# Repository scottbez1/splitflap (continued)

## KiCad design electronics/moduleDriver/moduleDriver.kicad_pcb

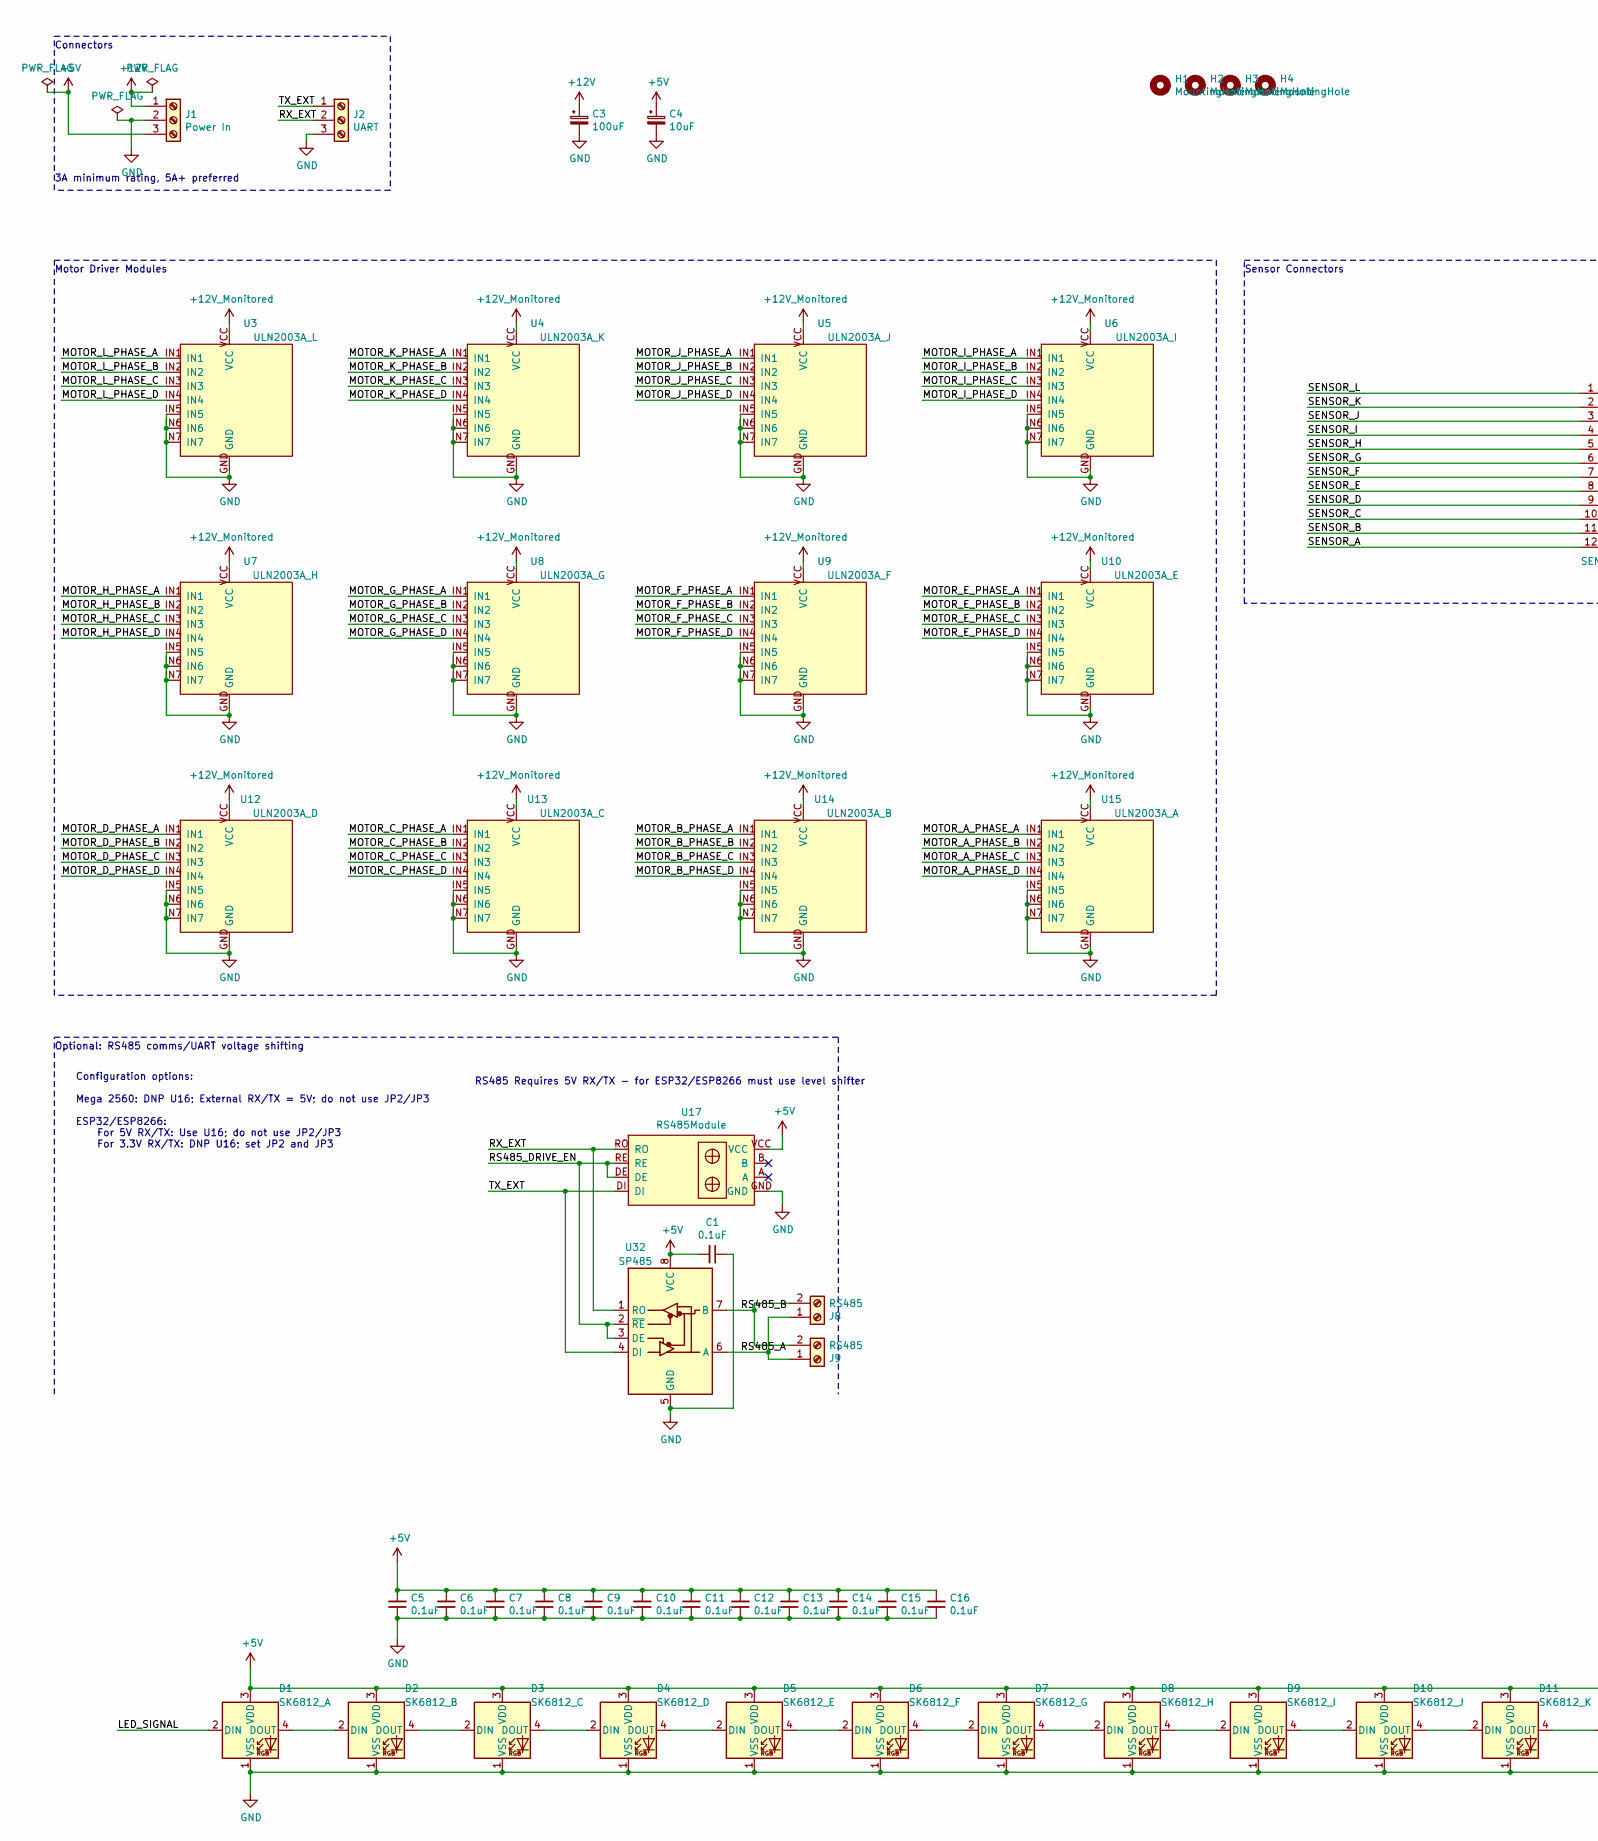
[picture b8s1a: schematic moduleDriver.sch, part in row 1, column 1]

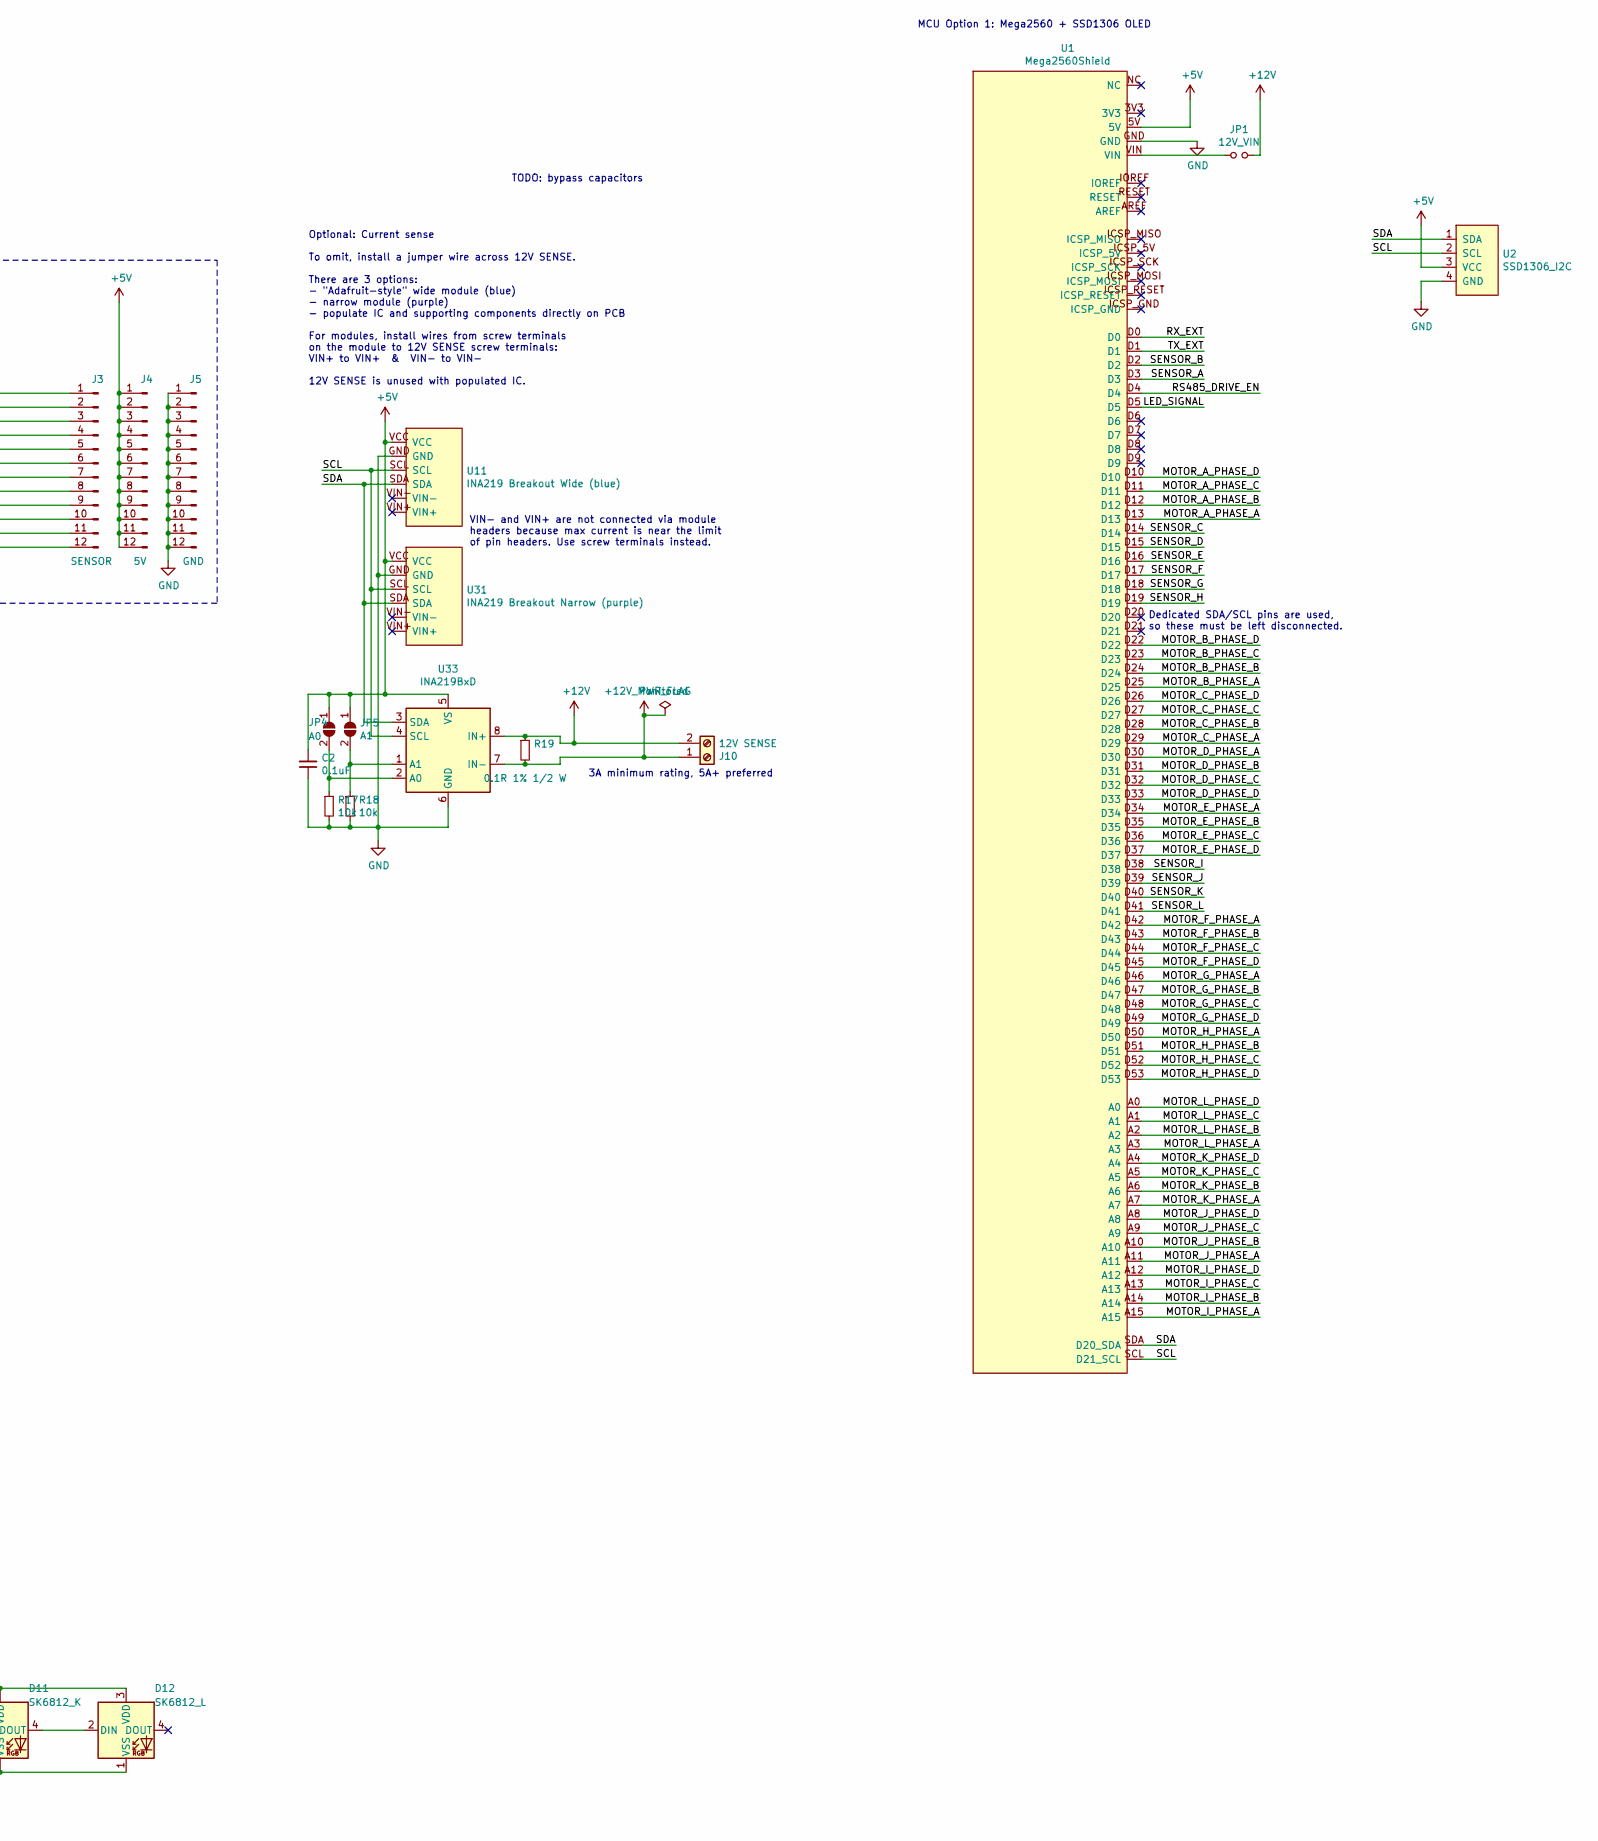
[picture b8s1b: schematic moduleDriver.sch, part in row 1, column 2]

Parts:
C1, C2, C5, C6, C7, C8, C9, C10, C11, C12, C13, C14, C15, C16: 0.1uF; C_0805_2012Metric_Pad1.15x1.40mm_HandSolder
C3: 100uF; CP_Radial_D10.0mm_P3.50mm
C4: 10uF; CP_Radial_D6.3mm_P2.50mm
D1: SK6812_A; LED_SK6812_PLCC4_5.0x5.0mm_P3.2mm
D2: SK6812_B; LED_SK6812_PLCC4_5.0x5.0mm_P3.2mm
D3: SK6812_C; LED_SK6812_PLCC4_5.0x5.0mm_P3.2mm
D4: SK6812_D; LED_SK6812_PLCC4_5.0x5.0mm_P3.2mm
D5: SK6812_E; LED_SK6812_PLCC4_5.0x5.0mm_P3.2mm
D6: SK6812_F; LED_SK6812_PLCC4_5.0x5.0mm_P3.2mm
D7: SK6812_G; LED_SK6812_PLCC4_5.0x5.0mm_P3.2mm
D8: SK6812_H; LED_SK6812_PLCC4_5.0x5.0mm_P3.2mm
D9: SK6812_I; LED_SK6812_PLCC4_5.0x5.0mm_P3.2mm
D10: SK6812_J; LED_SK6812_PLCC4_5.0x5.0mm_P3.2mm
D11: SK6812_K; LED_SK6812_PLCC4_5.0x5.0mm_P3.2mm
D12: SK6812_L; LED_SK6812_PLCC4_5.0x5.0mm_P3.2mm
H1, H2, H3, H4: MountingHole; MountingHole_4.3mm_M4_ISO7380_Pad
J1: Power In; TerminalBlock_bornier-3_P5.08mm
J2: UART; TerminalBlock_bornier-3_P5.08mm
J3: SENSOR; PinHeader_1x12_P2.54mm_Vertical
J4: 5V; PinHeader_1x12_P2.54mm_Vertical
J5: GND; PinHeader_1x12_P2.54mm_Vertical
J8, J9: RS485; TerminalBlock_bornier-2_P5.08mm
J10: 12V SENSE; TerminalBlock_bornier-2_P5.08mm
JP1: 12V_VIN; PinHeader_1x02_P2.54mm_Vertical
JP4: A0; SolderJumper-2_P1.3mm_Open_TrianglePad1.0x1.5mm
JP5: A1; SolderJumper-2_P1.3mm_Open_TrianglePad1.0x1.5mm
R17, R18: 10k; R_0805_2012Metric_Pad1.15x1.40mm_HandSolder
R19: 0.1R 1% 1/2 W; R_2512_6332Metric_Pad1.52x3.35mm_HandSolder
U1: Mega2560Shield; Mega2560Shield_Modified
U2: SSD1306_I2C; SSD1306_128x32
U3: ULN2003A_L; ULN2003AModule_No_EN_No_FSilk
U4: ULN2003A_K; ULN2003AModule_No_EN_No_FSilk
U5: ULN2003A_J; ULN2003AModule_No_EN_No_FSilk
U6: ULN2003A_I; ULN2003AModule_No_EN_No_FSilk
U7: ULN2003A_H; ULN2003AModule_No_EN_No_FSilk
U8: ULN2003A_G; ULN2003AModule_No_EN_No_FSilk
U9: ULN2003A_F; ULN2003AModule_No_EN_No_FSilk
U10: ULN2003A_E; ULN2003AModule_No_EN_No_FSilk
U11: INA219 Breakout Wide (blue); INA219_LARGE
U12: ULN2003A_D; ULN2003AModule_No_EN_No_FSilk
U13: ULN2003A_C; ULN2003AModule_No_EN_No_FSilk
U14: ULN2003A_B; ULN2003AModule_No_EN_No_FSilk
U15: ULN2003A_A; ULN2003AModule_No_EN_No_FSilk
U17: RS485Module
U31: INA219 Breakout Narrow (purple); INA219_SMALL
U32: SP485; SOIC-8_3.9x4.9mm_P1.27mm
U33: INA219BxD; SOIC-8_3.9x4.9mm_P1.27mm

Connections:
+5V: C1.2, C2.2, C4.1, C5.2, C6.2, C7.2, C8.2, C9.2, C10.2, C11.2, C12.2, C13.2, C14.2, C15.2, C16.2, D1.3 (VDD), D2.3 (VDD), D3.3 (VDD), D4.3 (VDD), D5.3 (VDD), D6.3 (VDD), D7.3 (VDD), D8.3 (VDD), D9.3 (VDD), D10.3 (VDD), D11.3 (VDD), D12.3 (VDD), J1.3, J4.1, J4.2, J4.3, J4.4, J4.5, J4.6, J4.7, J4.8, J4.9, J4.10, J4.11, J4.12, JP4.1 (A), JP5.1 (A), U1.5V, U2.3 (VCC), U11.VCC, U17.VCC, U31.VCC, U32.8 (VCC), U33.5 (VS)
+12V: C3.1, J1.1, J10.2, JP1.2, R19.1, U33.8 (IN+)
+12V_Monitored: J10.1, R19.2, U3.VCC, U4.VCC, U5.VCC, U6.VCC, U7.VCC, U8.VCC, U9.VCC, U10.VCC, U12.VCC, U13.VCC, U14.VCC, U15.VCC, U33.7 (IN-)
/LED_SIGNAL: D1.2 (DIN), U1.D5
/MOTOR_A_PHASE_A: U1.D13, U15.IN1
/MOTOR_A_PHASE_B: U1.D12, U15.IN2
/MOTOR_A_PHASE_C: U1.D11, U15.IN3
/MOTOR_A_PHASE_D: U1.D10, U15.IN4
/MOTOR_B_PHASE_A: U1.D25, U14.IN1
/MOTOR_B_PHASE_B: U1.D24, U14.IN2
/MOTOR_B_PHASE_C: U1.D23, U14.IN3
/MOTOR_B_PHASE_D: U1.D22, U14.IN4
/MOTOR_C_PHASE_A: U1.D29, U13.IN1
/MOTOR_C_PHASE_B: U1.D28, U13.IN2
/MOTOR_C_PHASE_C: U1.D27, U13.IN3
/MOTOR_C_PHASE_D: U1.D26, U13.IN4
/MOTOR_D_PHASE_A: U1.D30, U12.IN1
/MOTOR_D_PHASE_B: U1.D31, U12.IN2
/MOTOR_D_PHASE_C: U1.D32, U12.IN3
/MOTOR_D_PHASE_D: U1.D33, U12.IN4
/MOTOR_E_PHASE_A: U1.D34, U10.IN1
/MOTOR_E_PHASE_B: U1.D35, U10.IN2
/MOTOR_E_PHASE_C: U1.D36, U10.IN3
/MOTOR_E_PHASE_D: U1.D37, U10.IN4
/MOTOR_F_PHASE_A: U1.D42, U9.IN1
/MOTOR_F_PHASE_B: U1.D43, U9.IN2
/MOTOR_F_PHASE_C: U1.D44, U9.IN3
/MOTOR_F_PHASE_D: U1.D45, U9.IN4
/MOTOR_G_PHASE_A: U1.D46, U8.IN1
/MOTOR_G_PHASE_B: U1.D47, U8.IN2
/MOTOR_G_PHASE_C: U1.D48, U8.IN3
/MOTOR_G_PHASE_D: U1.D49, U8.IN4
/MOTOR_H_PHASE_A: U1.D50, U7.IN1
/MOTOR_H_PHASE_B: U1.D51, U7.IN2
/MOTOR_H_PHASE_C: U1.D52, U7.IN3
/MOTOR_H_PHASE_D: U1.D53, U7.IN4
/MOTOR_I_PHASE_A: U1.A15, U6.IN1
/MOTOR_I_PHASE_B: U1.A14, U6.IN2
/MOTOR_I_PHASE_C: U1.A13, U6.IN3
/MOTOR_I_PHASE_D: U1.A12, U6.IN4
/MOTOR_J_PHASE_A: U1.A11, U5.IN1
/MOTOR_J_PHASE_B: U1.A10, U5.IN2
/MOTOR_J_PHASE_C: U1.A9, U5.IN3
/MOTOR_J_PHASE_D: U1.A8, U5.IN4
/MOTOR_K_PHASE_A: U1.A7, U4.IN1
/MOTOR_K_PHASE_B: U1.A6, U4.IN2
/MOTOR_K_PHASE_C: U1.A5, U4.IN3
/MOTOR_K_PHASE_D: U1.A4, U4.IN4
/MOTOR_L_PHASE_A: U1.A3, U3.IN1
/MOTOR_L_PHASE_B: U1.A2, U3.IN2
/MOTOR_L_PHASE_C: U1.A1, U3.IN3
/MOTOR_L_PHASE_D: U1.A0, U3.IN4
/RS485_A: J8.1, J9.1, U32.6 (A)
/RS485_B: J8.2, J9.2, U32.7 (B)
/RS485_DRIVE_EN: U1.D4, U17.DE, U17.RE, U32.2 (~RE), U32.3 (DE)
/RX_EXT: J2.2, U1.D0, U17.RO, U32.1 (RO)
/SCL: U1.SCL (D21_SCL), U2.2 (SCL), U11.SCL, U31.SCL, U33.4 (SCL)
/SDA: U1.SDA (D20_SDA), U2.1 (SDA), U11.SDA, U31.SDA, U33.3 (SDA)
/SENSOR_A: J3.12, U1.D3
/SENSOR_B: J3.11, U1.D2
/SENSOR_C: J3.10, U1.D14
/SENSOR_D: J3.9, U1.D15
/SENSOR_E: J3.8, U1.D16
/SENSOR_F: J3.7, U1.D17
/SENSOR_G: J3.6, U1.D18
/SENSOR_H: J3.5, U1.D19
/SENSOR_I: J3.4, U1.D38
/SENSOR_J: J3.3, U1.D39
/SENSOR_K: J3.2, U1.D40
/SENSOR_L: J3.1, U1.D41
/TX_EXT: J2.1, U1.D1, U17.DI, U32.4 (DI)
GND: C1.1, C2.1, C3.2, C4.2, C5.1, C6.1, C7.1, C8.1, C9.1, C10.1, C11.1, C12.1, C13.1, C14.1, C15.1, C16.1, D1.1 (VSS), D2.1 (VSS), D3.1 (VSS), D4.1 (VSS), D5.1 (VSS), D6.1 (VSS), D7.1 (VSS), D8.1 (VSS), D9.1 (VSS), D10.1 (VSS), D11.1 (VSS), D12.1 (VSS), J1.2, J2.3, J5.1, J5.2, J5.3, J5.4, J5.5, J5.6, J5.7, J5.8, J5.9, J5.10, J5.11, J5.12, R17.2, R18.2, U1.GND, U2.4 (GND), U3.GND, U3.IN5, U3.IN6, U3.IN7, U4.GND, U4.IN5, U4.IN6, U4.IN7, U5.GND, U5.IN5, U5.IN6, U5.IN7, U6.GND, U6.IN5, U6.IN6, U6.IN7, U7.GND, U7.IN5, U7.IN6, U7.IN7, U8.GND, U8.IN5, U8.IN6, U8.IN7, U9.GND, U9.IN5, U9.IN6, U9.IN7, U10.GND, U10.IN5, U10.IN6, U10.IN7, U11.GND, U12.GND, U12.IN5, U12.IN6, U12.IN7, U13.GND, U13.IN5, U13.IN6, U13.IN7, U14.GND, U14.IN5, U14.IN6, U14.IN7, U15.GND, U15.IN5, U15.IN6, U15.IN7, U17.GND, U31.GND, U32.5 (GND), U33.6 (GND)
unnamed: D1.4 (DOUT), D2.2 (DIN)
unnamed: D2.4 (DOUT), D3.2 (DIN)
unnamed: D3.4 (DOUT), D4.2 (DIN)
unnamed: D4.4 (DOUT), D5.2 (DIN)
unnamed: D5.4 (DOUT), D6.2 (DIN)
unnamed: D6.4 (DOUT), D7.2 (DIN)
unnamed: D7.4 (DOUT), D8.2 (DIN)
unnamed: D8.4 (DOUT), D9.2 (DIN)
unnamed: D9.4 (DOUT), D10.2 (DIN)
unnamed: D10.4 (DOUT), D11.2 (DIN)
unnamed: D11.4 (DOUT), D12.2 (DIN)
unnamed: JP1.1, U1.VIN
unnamed: JP4.2 (B), R17.1, U33.2 (A0)
unnamed: JP5.2 (B), R18.1, U33.1 (A1)

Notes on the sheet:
MCU Option 1: Mega2560 + SSD1306 OLED
Optional: RS485 comms/UART voltage shifting
Motor Driver Modules
Sensor Connectors
Optional: Current sense To omit, install a jumper wire across 12V SENSE. There are 3 options: - "Adafruit-style" wide module (blue) - narrow module (purple) - populate IC and supporting components directly on PCB For modules, install wires from screw terminals on the module to 12V SENSE screw termi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
Connectors
Configuration options: Mega 2560: DNP U16; External RX/TX = 5V; do not use JP2/JP3 ESP32/ESP8266: For 5V RX/TX: Use U16; do not use JP2/JP3 For 3.3V RX/TX: DNP U16; set JP2 and JP3
RS485 Requires 5V RX/TX - for ESP32/ESP8266 must use level shifter
VIN- and VIN+ are not connected via module headers because max current is near the limit of pin headers. Use screw terminals instead.
3A minimum rating, 5A+ preferred
TODO: bypass capacitors
Dedicated SDA/SCL pins are used, so these must be left disconnected.

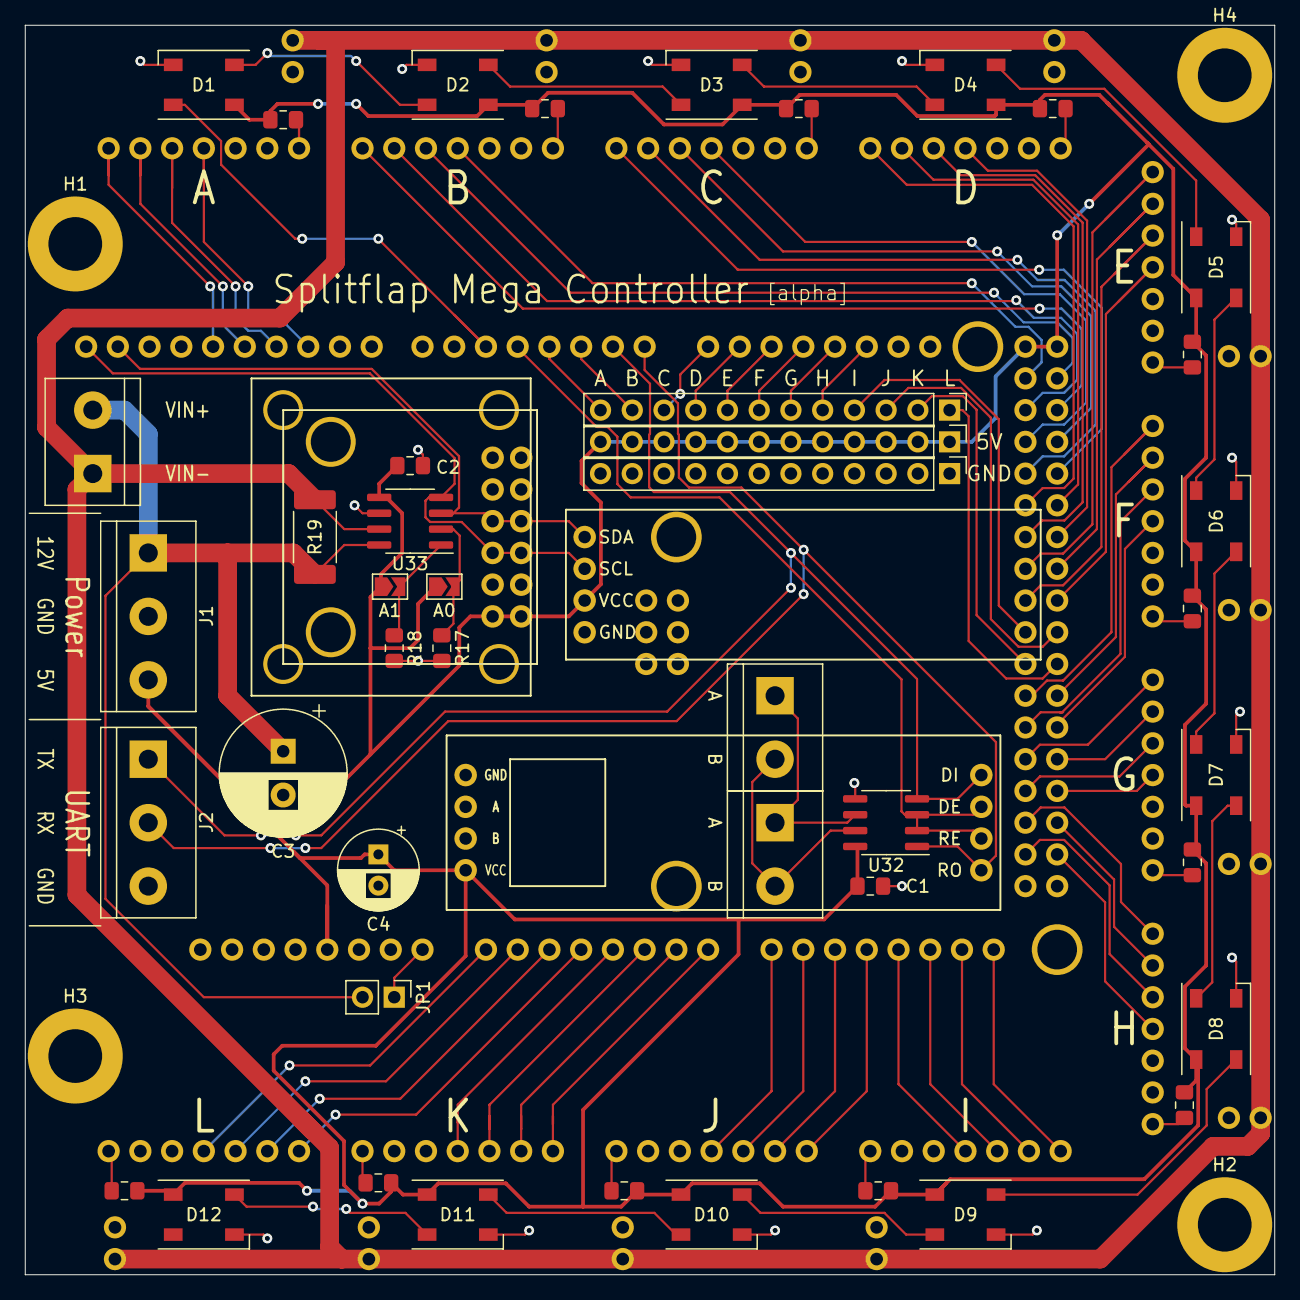
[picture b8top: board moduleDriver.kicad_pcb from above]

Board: 2 copper layers, 100.0 x 100.0 mm, 65 parts (0 on the bottom side), 86 nets.

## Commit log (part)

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2021-07-07 Barcode scanner integrated
2021-07-07 Fix JWT for Google APIs, basic working API call
2021-07-07 WIP combined front panel
2021-07-07 More correct flap positioning
2021-07-11 Generate conditional corners for fillet tool 3D
2021-07-11 Add support for additive 3D fillets
2021-07-11 Refactor pcb_mount as classic_pcb_mount
    Distinguishing between the "classic" driver and the new "chainlink" driver.
2021-07-12 Basic working test result reporting to Firestore
2021-07-13 Fix flapIndex in display_task, install example secrets when building chainlinkDriverTester
2021-07-15 3d: Fix extraneous PCB in the PCB case design
2021-07-18 Update references to artifacts
2021-07-18 Add $fn parameter to have smoother edges when generating svg fonts (#168)
    At the current state, when you use the `generate_font.py` file, the generated svgs are quite low poly. This is due to the facet number on `facet.scad` is set 0 as default.
    If we look at the image below, the first one is what you would get if you generated the fonts. I tried 60, but it's not quite smooth enough. So I just doubled the value and tried 120. 120 gave me cle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
    But the [docs ](https://en.wikibooks.org/wiki/OpenSCAD_User_Manual/Other_Language_Features#.24fa.2C_.24fs_and_.24fn) don't recommend going beyond 100, so this pull request is using 100.
    ![difference_resolution](ht
2021-07-23 Software: init with default character list
    This allows rudimentary character filtering even if the display has yet to connect
2021-07-29 Software: Add backticks around destinations
2021-08-01 Front panel generation improvements (#173)
    - Add `--center-window` option to vertically center the modules based on their window, rather than the default of centering based on flap/letter centers
    - Improve export performance drastically by omitting the 3d splitflap modules entire in projection rendering mode
    - Fix `--center-center-x` and `--center-center-y` arguments
    - Change dog bone shape (and front face M4 hole) to rectangles to simplify the 2d geometry that's exported for external CAM (Fusion 360 did not perform well with all of the polygon-ized cricles)
2021-08-04 Modifications from ponoko test and for elecrow acrylic
2021-08-26 Log some useful values when generating combined front panels
2021-09-03 WIP chainlinkBase firmware
2021-09-21 Refactor almost all serial to serial task, add display layouts
2021-10-01 Basic functional bidirectional PB protocol
2021-10-01 set flaps with strings
2021-10-02 Add serial acks and retries
2021-10-05 splitflapjs util for mapping chainlink ordering to 2d layout, re-export protobuf types
2021-10-06 Major rewrite of supervisor task as a state machine, add supervisor state reporting via proto
2021-10-20 Add side-by-side option for rendering font/flap designs
2021-10-20 Revert some CodeART-specific mods
2021-10-20 Clean up platformio defaults
2021-10-25 Enclosure: Bias side tabs to break symmetry
2021-10-26 Fix connector placement in 2d export after side tab changes
2021-10-27 Add side-by-side option for rendering font/flap designs (#186)
2021-10-27 Thickness
2021-10-29 Initial Chainlink Buddy T-Display
2021-10-31 Chainlink Buddy T-Display prep
2021-10-31 Chainlink Driver Tester IDC conversion, change all pogo pins to 1mm and decrease clearance
2021-11-01 fix github actions
2021-11-01 Change Chainlink data connections from screw terminals to IDC (#189)
    - Replace screw terminals with 2x4 IDC connectors (alternating ground) on Driver, Base, and Tester. Fixes #179
    - Change Chainlink Driver Tester to all 1mm pogo pins
    - Create new "Buddy" boards for connecting IDC/ribbon cable to T-Display or a breadboard
    - Big readme cleanup and reorganization for clarity (hopefully!)
2021-11-02 Label sensor PCB v1.1 and add 3d models
2021-11-02 Add dimensions to Chainlink Buddy T-Display
2021-12-01 New weather api, message cycling, display auto-sizing, serial protocol switching
2021-12-01 HTTP polling example, memory reduction (to make room for TLS), various display improvements, serial protocol switching (#191)
    This was primarily an implementation of an HTTP API example, but during testing I ended up fixing a bunch of other things too. The biggest roadblock was running out of heap space for TLS (HTTPS), whi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
    Changes:
    - add HTTPTask and implement example:
    - fetch weather data for San Francisco
    - parse and process data (using json11) to calculate median temperature and wind speed across multiple weather stations
    - generate 2 separate messages (temp and wind speed) to be displayed
2021-12-01 Add debug messages to LCD display, NTP and show wifi info in HTTP example
2022-01-14 WIP python proto library
2022-01-15 Basic working python proto lib with example
2022-02-21 First pass at Windows support, and Inkscape 1.0 CLI
2022-03-31 Bump minimist from 1.2.5 to 1.2.6 in /software/js/splitflapjs
    Bumps [minimist](https://github.com/substack/minimist) from 1.2.5 to 1.2.6.
    - [Release notes](https://github.com/substack/minimist/releases)
    - [Commits](https://github.com/substack/minimist/compare/1.2.5...1.2.6)
    ---
    updated-dependencies:
    - dependency-name: minimist
2022-04-02 Add vertical keepout clip option to generate_fonts.py
2022-04-07 Moved Design Into Documentation/Design.md
2022-04-07 Direct Links -> Link References
2022-04-08 Bump minimist from 1.2.5 to 1.2.6 in /software/chainlink/js/example
    Bumps [minimist](https://github.com/substack/minimist) from 1.2.5 to 1.2.6.
    - [Release notes](https://github.com/substack/minimist/releases)
    - [Commits](https://github.com/substack/minimist/compare/1.2.5...1.2.6)
    ---
    updated-dependencies:
    - dependency-name: minimist
2022-04-08 Bump minimist from 1.2.5 to 1.2.6 in /software/chainlink/js/splitflapjs
    Bumps [minimist](https://github.com/substack/minimist) from 1.2.5 to 1.2.6.
    - [Release notes](https://github.com/substack/minimist/releases)
    - [Commits](https://github.com/substack/minimist/compare/1.2.5...1.2.6)
    ---
    updated-dependencies:
    - dependency-name: minimist
2022-08-12 Output enable ChainlinkDriver
2022-08-20 Started shifting connectors outward, locking header pin footprint
2023-01-03 Slack -> Discord
2023-07-12 WIP npm workspaces and web serial JS
2023-07-14 idle messages
2023-10-09 Improve web serial example
2023-10-09 Update package-lock
2023-10-09 Show link to project page if web serial isn't supported too
2023-12-01 Bump @adobe/css-tools from 4.3.1 to 4.3.2 in /software/chainlink/js
    Bumps [@adobe/css-tools](https://github.com/adobe/css-tools) from 4.3.1 to 4.3.2.
    - [Changelog](https://github.com/adobe/css-tools/blob/main/History.md)
    - [Commits](https://github.com/adobe/css-tools/commits)
    ---
    updated-dependencies:
    - dependency-name: "@adobe/css-tools"
2024-01-14 fix stl export
2024-01-15 typo
2024-01-20 new sensor pcb checkin
2024-02-20 Remove zip tie option, improve elecrow output
2024-03-08 Update kikit for sensor_smd
2024-03-09 kibot for v6
2024-03-09 Adjust filters
2024-03-09 default empty alt-fields
2024-03-09 Versioned file for kicad variables
2024-03-09 Fix baketext
2024-03-09 CI/readme updates
2024-03-09 Fix filenames
2024-03-24 Simplify splitflap_module and add basic offset support
2024-03-30 WIP exposing offset via proto
2024-04-11 WebSerial demo - remove idle messages, add checkbox for forcing full rotations
2024-05-25 flap_container.scad: use flap.scad
    Otherwise we get warnings, and things won't render!
    ```
    WARNING: Ignoring unknown module 'flap_2d' in file flap_container.scad, line 76
    WARNING: Ignoring unknown module 'flap_2d' in file flap_container.scad, line 118
    ```
2024-06-08 Log debug build info at startup
2024-06-11 Initial GeneralState concept
2024-06-13 README updates, extract module dimensions and panel dimensions, attempt including them in readme
2024-06-13 Disable inter-module-connectors on default exports
2024-06-14 Prep for merge to master
2024-06-14 fix sensor section in README
2024-06-20 generate_2d.py: inkscape resize handle newer inkscape versions dropping 'verb' support
2024-08-13 [webserial example] Remove idle demo
2024-09-01 Add/fix proper v2 character set
2024-09-01 Get character set from display
2024-10-05 Missed some updates
2024-10-06 Strict version check
2024-10-06 flap_container.scad: use flap.scad (#235)
    Otherwise we get warnings, and things won't render!
    ```
    WARNING: Ignoring unknown module 'flap_2d' in file flap_container.scad, line 76
    WARNING: Ignoring unknown module 'flap_2d' in file flap_container.scad, line 118
    ```
2024-10-06 Repack components to fit within 20x20cm (#238)
    As promised, here's a PR with the edits I made!
    I removed the `spools_too_big` variable as well, which simplifies the
    logic a little bit.
2024-10-06 Fix pio commands in CI
2024-10-06 Add link to v2 assembly guide
2024-11-10 Make connector less fragile, move inside top/bottom enclosure
2024-12-26 Reduce clearance, negative depth clearance due to fillets
2025-01-19 Replace paper links
2025-01-20 More doc updates, including importing the flap info from the wiki
2025-01-22 an addition to PR #240 (#247)
    realised, this part was not in the PR from before as I had it in my own
    secrets.h which is in the .gitignore file
2025-01-23 Run generate_combined_front_panel and generate_fonts in CI (#250)
    * Run generate_combined_front_panel.py and generate_fonts.py in CI, to
    generate example artifacts
    * Add raster rendering option to those scripts
    * fix font generation (missing `use` in font_generator.scad)
2025-01-26 More placement adjustments
2025-01-26 WIP updating parts for assembly
2025-02-13 ignore .vscode
2025-02-15 add generator for single flap
2025-02-19 fix(ci): bump action versions to fix JS workflow
    Since 2025-01-30 the JS workflow has been failing with:
    This request has been automatically failed because it uses a deprecated version of `actions/upload-artifact: v3`.
    Learn more: https://github.blog/changelog/2024-04-16-deprecation-notice-v3-of-the-artifact-actions/
    This commit bumps two action versions to repair the workflow.
2025-03-05 Update OrderingComplete.md
    Some suggested improvements from "hi2hello" in discord
2025-03-29 Flap generation for 3d printing: subtract out the letters from the flap shape
2025-05-13 Avoid SPI input glitches from wifi (#263)
    # Changes
    * Disable WiFi power saving to avoid sensor data glitches
    * Also update platformio espressif platform which was very outdated
    (note: this may result in a flash rewrite that wipes saved module
    calibration data!)
    # Motivation
2025-05-18 wip more home assistant
2025-08-10 default to home if unspecified
